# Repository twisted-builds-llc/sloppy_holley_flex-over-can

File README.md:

# Sloppy Holley Flex-over-CAN

CAN bus input/output module for Holley Terminator X (also HP/Dominator class ECUs).

- **To Holley:** GM/Continental flex-fuel sensor (ethanol % + fuel temp) and four 0-5 V analog inputs, sent as CAN device 1985.
- **From Holley:** four low-side (ground-switching) outputs, each on/off or PWM, following Holley I/O output rows.
- ESP32-C3-WROOM-02, WiFi AP web panel for status/config/test, USB-C for flashing.
- Built for JLCPCB assembly.

> Status: early development. See [docs/PROGRESS.md](docs/PROGRESS.md).
> Never use for engine control until the bench and engine-off validations in PROGRESS.md are complete.

## Connector (J1, HCCPHPE24BKA90F, 24 pin)

Cavity names are the J1 footprint pad names (rows A, B, C). Use them when building the harness.

| Cavity | Function | Cavity | Function | Cavity | Function |
|-------:|----------|-------:|----------|-------:|----------|
| A1 | +12 V in | B1 | Power GND | C1 | Output 3 (low side) |
| A2 | CAN H | B2 | +5 V sensor | C2 | +5 V sensor |
| A3 | CAN L | B3 | Analog 1 signal | C3 | Analog 3 signal |
| A4 | Flex sensor +12 V out | B4 | Sensor GND | C4 | Sensor GND |
| A5 | Flex sensor signal | B5 | +5 V sensor | C5 | +5 V sensor |
| A6 | Flex sensor GND | B6 | Analog 2 signal | C6 | Analog 4 signal |
| A7 | Power GND | B7 | Sensor GND | C7 | Sensor GND |
| A8 | Output 1 (low side) | B8 | Output 2 (low side) | C8 | Output 4 (low side) |

Output load current returns through A7 and B1. Sensor grounds (A6, B4, B7, C4, C7) are a separate quiet ground joined to power GND at one point on the board.

## Web panel

The module runs its own WiFi access point, `FLEXCAN-XXXX`. Each board makes a random password on first boot. Type `WIFI` on the USB serial console (115200) to see it. Then open http://192.168.4.1. The panel shows status and has controls for AUTO / ALL OFF, a 30 s output test, the Holley row for each output, and the WiFi password.

## Repository layout

| Path | Contents |
|------|----------|
| `docs/PROGRESS.md` | Phase checklist, work log, open questions |
| `docs/CAN_PROTOCOL.md` | Holley CAN IDs and encodings, marked verified or hypothesis |
| `docs/HARDWARE.md` | Block diagram, GPIO map, part choices |
| `firmware/` | PlatformIO project (VS Code) |
| `Sloppy_Holley_Flex-over-can/` | KiCad project and project-local libraries |
| `Holley_Canbus_info/` | Reference only: Holley CAN doc, DBC, and the two bench prototypes (`CANFLEXPDU_WiFi_Ver12`, `CAN_Flex_Slim_Ver5`) |

## Firmware build

Install the PlatformIO extension in VS Code, then open the `firmware/` folder. From a terminal:

```sh
cd firmware
pio run                 # build
pio run -t upload       # flash over USB-C
pio device monitor      # serial at 115200
pio test -e native      # host unit tests
```

The ESP32 platform is pinned to an exact release in `platformio.ini`. All code beyond the Arduino-ESP32 core lives in this repo, so a third-party library update cannot change the build.

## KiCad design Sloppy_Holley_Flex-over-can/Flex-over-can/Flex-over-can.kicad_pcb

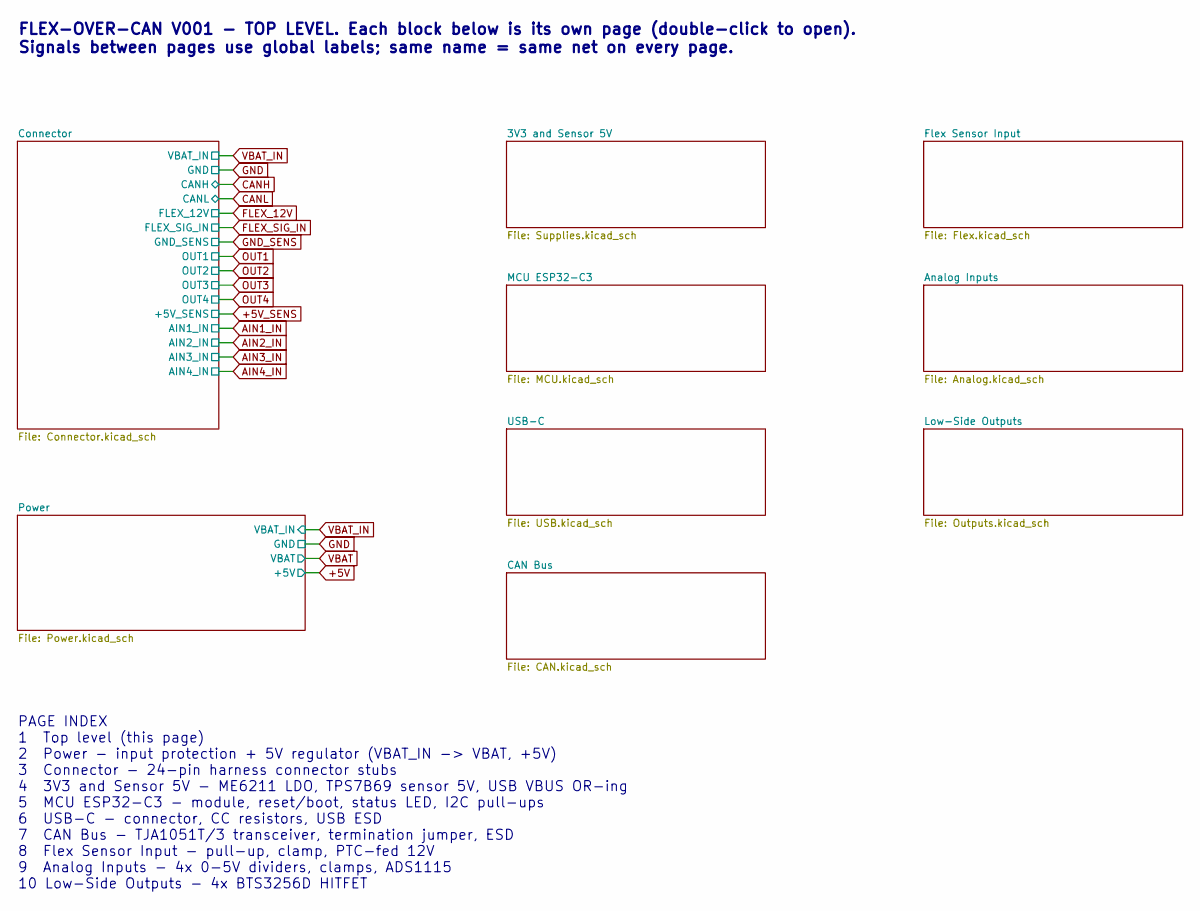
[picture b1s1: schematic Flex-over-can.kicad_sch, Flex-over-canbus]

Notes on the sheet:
PAGE INDEX 1 Top level (this page) 2 Power - input protection + 5V regulator (VBAT_IN -> VBAT, +5V) 3 Connector - 24-pin harness connector stubs 4 3V3 and Sensor 5V - ME6211 LDO, TPS7B69 sensor 5V, USB VBUS OR-ing 5 MCU ESP32-C3 - module, reset/boot, status LED, I2C pull-ups 6 USB-C - connector, CC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
FLEX-OVER-CAN V001 - TOP LEVEL. Each block below is its own page (double-click to open). Signals between pages use global labels; same name = same net on every page.

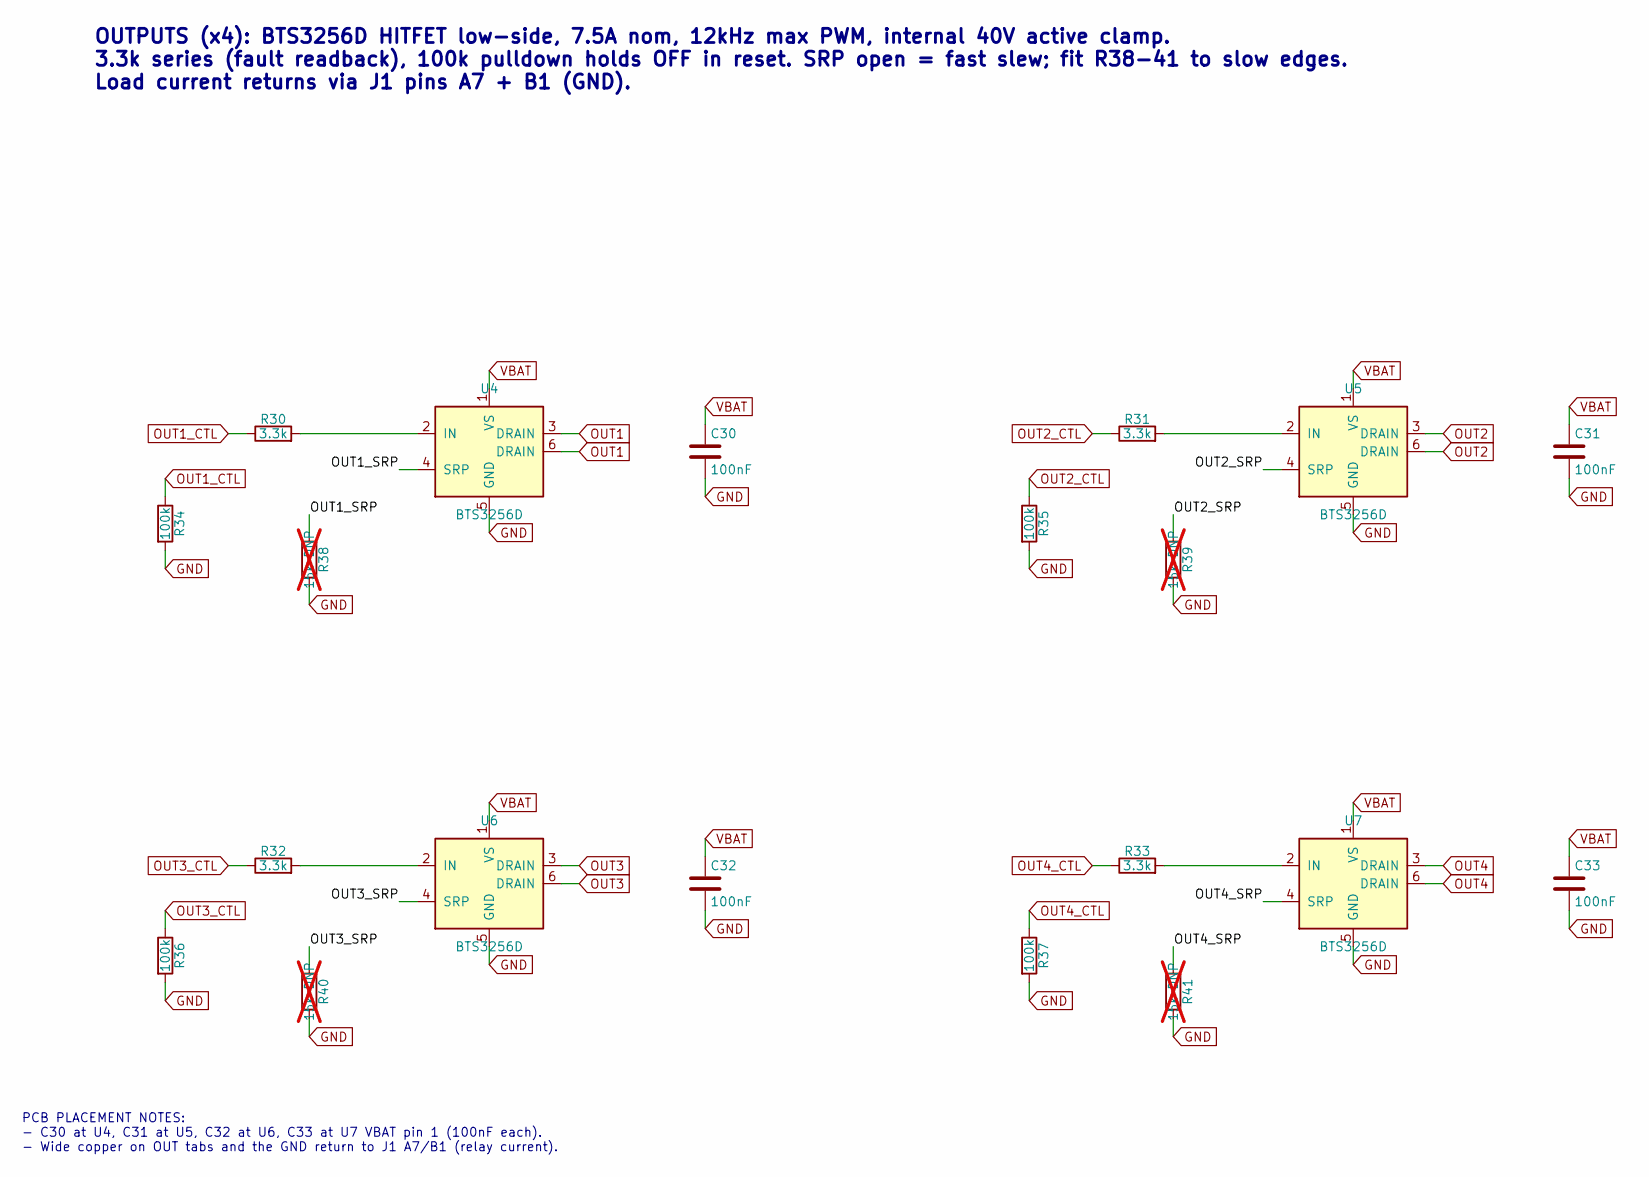
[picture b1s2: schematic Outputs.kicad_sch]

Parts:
C30, C31, C32, C33: 100nF; C_0603_1608Metric; LCSC C14663
R30, R31, R32, R33: 3.3k; R_0603_1608Metric; LCSC C22978
R34, R35, R36, R37: 100k; R_0603_1608Metric; LCSC C25803
R38, R39, R40, R41: 15k DNP; R_0603_1608Metric; LCSC C22809; not fitted
U4, U5, U6, U7: BTS3256D; TO-252-5_TabPin6; LCSC C3232337

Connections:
/Low-Side Outputs/OUT1_SRP: R38.1, U4.4 (SRP)
/Low-Side Outputs/OUT2_SRP: R39.1, U5.4 (SRP)
/Low-Side Outputs/OUT3_SRP: R40.1, U6.4 (SRP)
/Low-Side Outputs/OUT4_SRP: R41.1, U7.4 (SRP)
GND: C30.2, C31.2, C32.2, C33.2, R34.2, R35.2, R36.2, R37.2, R38.2, R39.2, R40.2, R41.2, U4.5 (GND), U5.5 (GND), U6.5 (GND), U7.5 (GND); also elsewhere on the board
unnamed: R30.2, U4.2 (IN)
unnamed: R31.2, U5.2 (IN)
unnamed: R32.2, U6.2 (IN)
unnamed: R33.2, U7.2 (IN)
OUT1: U4.3 (DRAIN), U4.6 (DRAIN); also elsewhere on the board
OUT1_CTL: R30.1, R34.1; also elsewhere on the board
OUT2: U5.3 (DRAIN), U5.6 (DRAIN); also elsewhere on the board
OUT2_CTL: R31.1, R35.1; also elsewhere on the board
OUT3: U6.3 (DRAIN), U6.6 (DRAIN); also elsewhere on the board
OUT3_CTL: R32.1, R36.1; also elsewhere on the board
OUT4: U7.3 (DRAIN), U7.6 (DRAIN); also elsewhere on the board
OUT4_CTL: R33.1, R37.1; also elsewhere on the board
VBAT: C30.1, C31.1, C32.1, C33.1, U4.1 (VS), U5.1 (VS), U6.1 (VS), U7.1 (VS); also elsewhere on the board

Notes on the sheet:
PCB PLACEMENT NOTES: - C30 at U4, C31 at U5, C32 at U6, C33 at U7 VBAT pin 1 (100nF each). - Wide copper on OUT tabs and the GND return to J1 A7/B1 (relay current).
OUTPUTS (x4): BTS3256D HITFET low-side, 7.5A nom, 12kHz max PWM, internal 40V active clamp. 3.3k series (fault readback), 100k pulldown holds OFF in reset. SRP open = fast slew; fit R38-41 to slow edges. Load current returns via J1 pins A7 + B1 (GND).

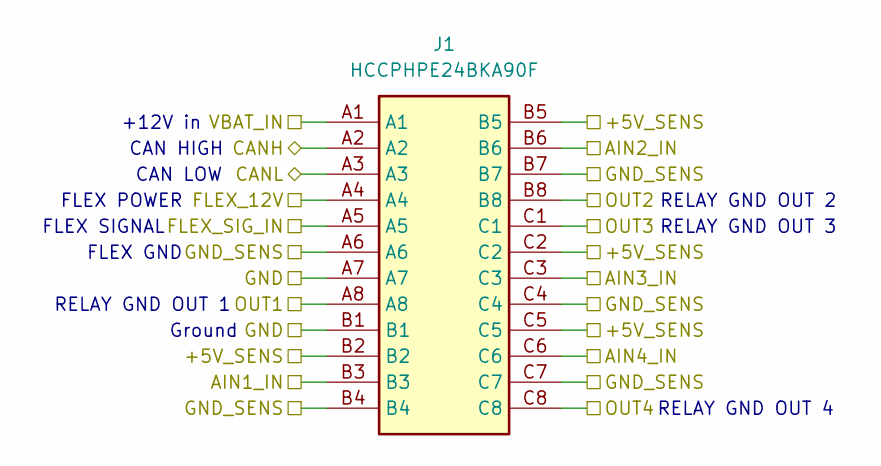
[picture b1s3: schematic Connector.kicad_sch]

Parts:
J1: HCCPHPE24BKA90F; 24pinConnectorFootprint; Manufacturer_Part_Number HCCPHPE24BKA90F; Mouser Part Number 649-HCCPHPE24BKA90F

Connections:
+5V_SENS: J1.B2, J1.B5, J1.C2, J1.C5; also elsewhere on the board
AIN1_IN: J1.B3; also elsewhere on the board
AIN2_IN: J1.B6; also elsewhere on the board
AIN3_IN: J1.C3; also elsewhere on the board
AIN4_IN: J1.C6; also elsewhere on the board
CANH: J1.A2; also elsewhere on the board
CANL: J1.A3; also elsewhere on the board
FLEX_12V: J1.A4; also elsewhere on the board
FLEX_SIG_IN: J1.A5; also elsewhere on the board
GND: J1.A7, J1.B1; also elsewhere on the board
GND_SENS: J1.A6, J1.B4, J1.B7, J1.C4, J1.C7; also elsewhere on the board
OUT1: J1.A8; also elsewhere on the board
OUT2: J1.B8; also elsewhere on the board
OUT3: J1.C1; also elsewhere on the board
OUT4: J1.C8; also elsewhere on the board
VBAT_IN: J1.A1; also elsewhere on the board

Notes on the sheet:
FLEX SIGNAL
RELAY GND OUT 2
+12V in
FLEX GND
RELAY GND OUT 3
Ground
CAN HIGH
RELAY GND OUT 1
FLEX POWER
CAN LOW
RELAY GND OUT 4

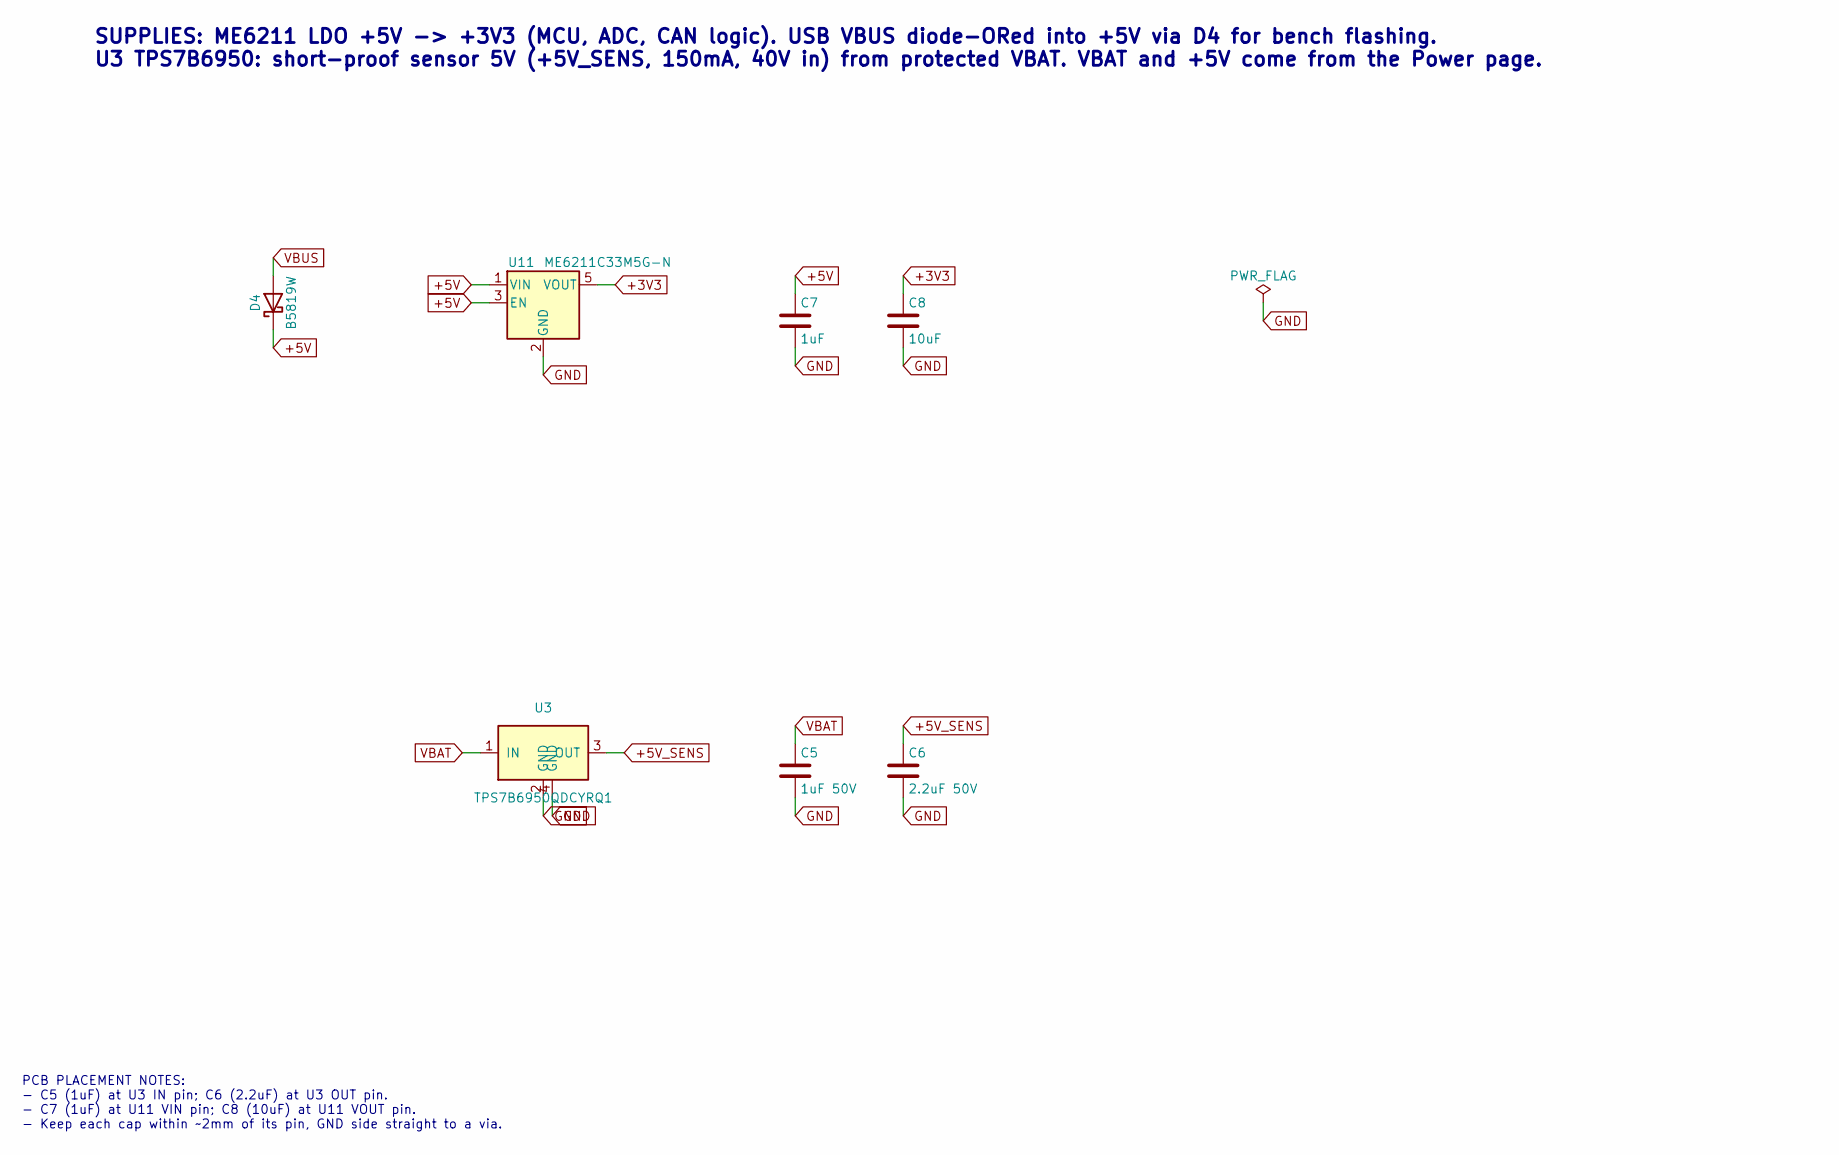
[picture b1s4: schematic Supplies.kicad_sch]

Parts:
C5: 1uF 50V; C_0805_2012Metric; LCSC C28323
C6: 2.2uF 50V; C_0805_2012Metric; LCSC C377773
C7: 1uF; C_0603_1608Metric; LCSC C15849
C8: 10uF; C_0603_1608Metric; LCSC C19702
D4: B5819W; D_SOD-123; LCSC C2943878
U3: TPS7B6950QDCYRQ1; SOT-223; LCSC C108469
U11: ME6211C33M5G-N; SOT-23-5; LCSC C82942

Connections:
+3V3: C8.1, U11.5 (VOUT); also elsewhere on the board
+5V: C7.1, D4.1 (K), U11.1 (VIN), U11.3 (EN); also elsewhere on the board
+5V_SENS: C6.1, U3.3 (OUT); also elsewhere on the board
GND: C5.2, C6.2, C7.2, C8.2, U3.2 (GND), U3.4 (GND), U11.2 (GND); also elsewhere on the board
VBAT: C5.1, U3.1 (IN); also elsewhere on the board
VBUS: D4.2 (A); also elsewhere on the board

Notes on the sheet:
PCB PLACEMENT NOTES: - C5 (1uF) at U3 IN pin; C6 (2.2uF) at U3 OUT pin. - C7 (1uF) at U11 VIN pin; C8 (10uF) at U11 VOUT pin. - Keep each cap within ~2mm of its pin, GND side straight to a via.
SUPPLIES: ME6211 LDO +5V -> +3V3 (MCU, ADC, CAN logic). USB VBUS diode-ORed into +5V via D4 for bench flashing. U3 TPS7B6950: short-proof sensor 5V (+5V_SENS, 150mA, 40V in) from protected VBAT. VBAT and +5V come from the Power page.

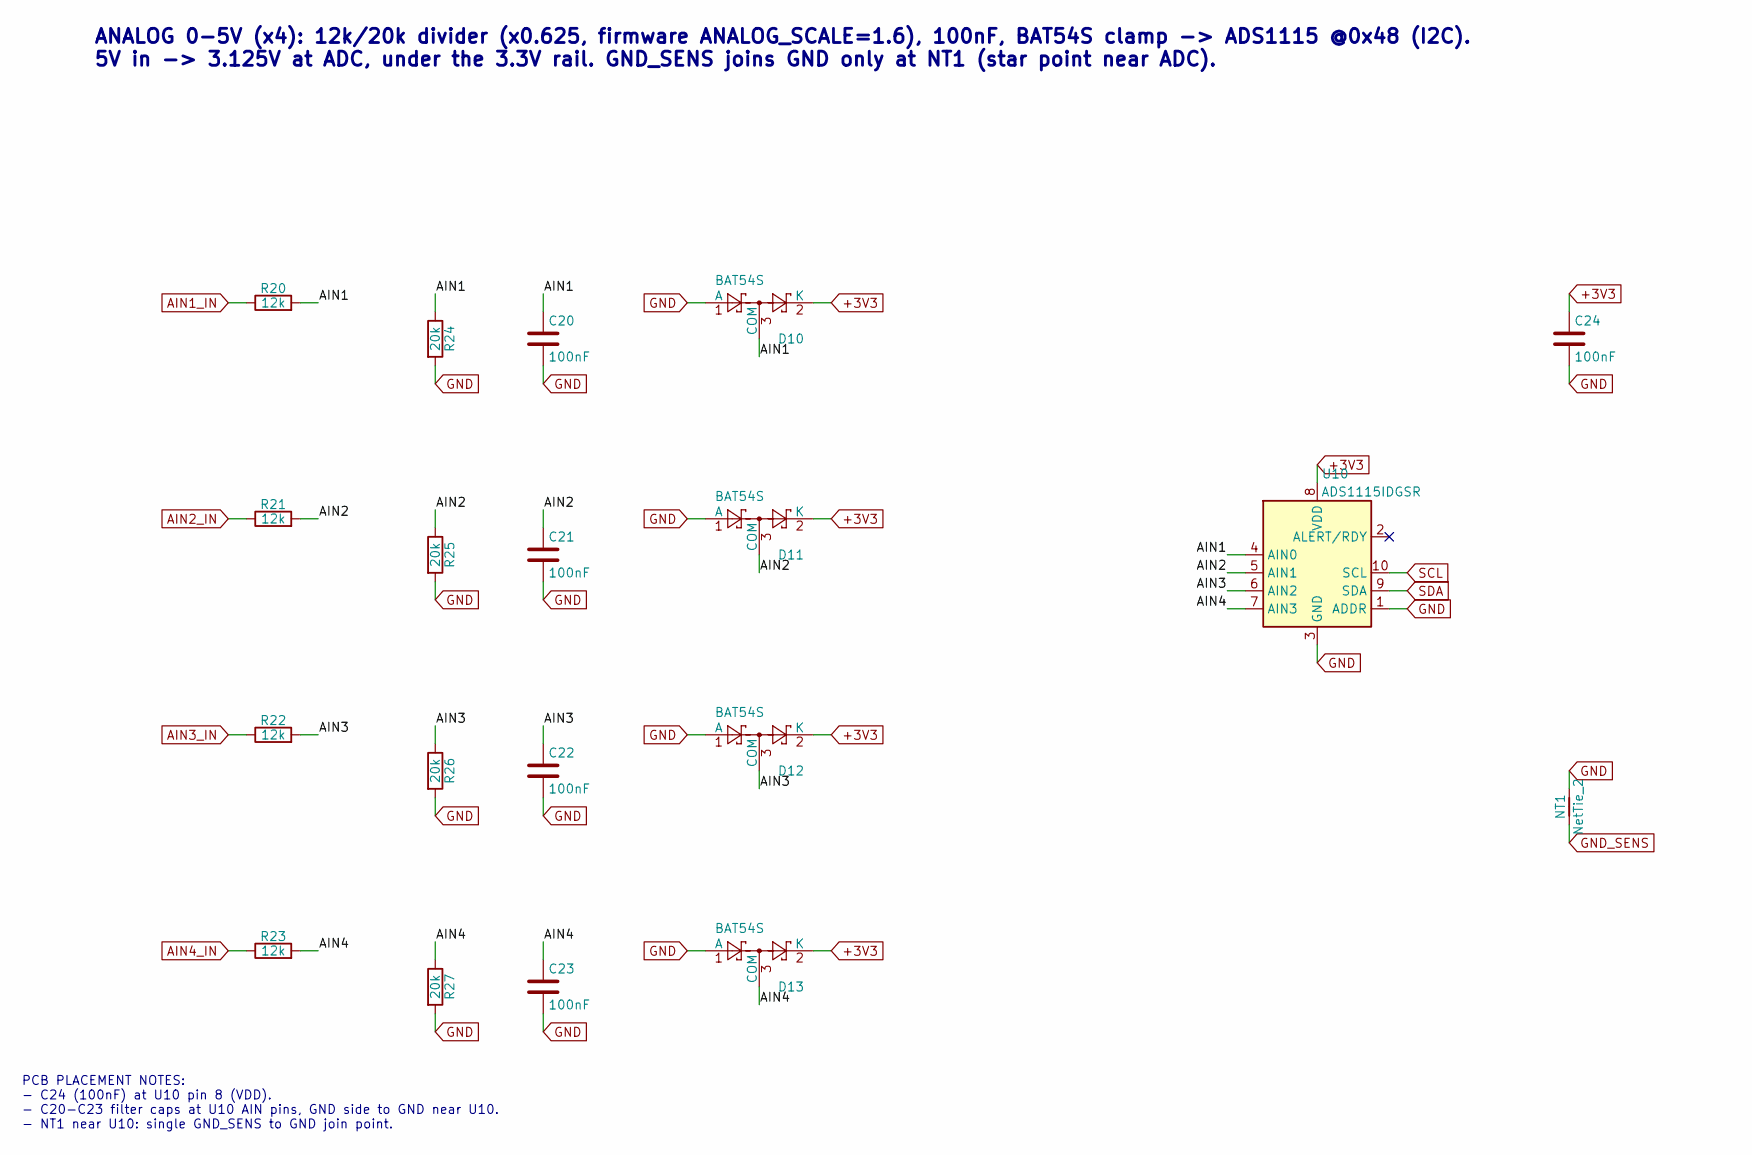
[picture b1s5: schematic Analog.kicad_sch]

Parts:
C20, C21, C22, C23, C24: 100nF; C_0603_1608Metric; LCSC C14663
D10, D11, D12, D13: BAT54S; SOT-23; LCSC C7420333
NT1: NetTie_2; NetTie-2_SMD_Pad0.5mm
R20, R21, R22, R23: 12k; R_0603_1608Metric; LCSC C22790
R24, R25, R26, R27: 20k; R_0603_1608Metric; LCSC C4184
U10: ADS1115IDGSR; TSSOP-10_3x3mm_P0.5mm; LCSC C37593

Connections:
+3V3: C24.1, D10.2 (K), D11.2 (K), D12.2 (K), D13.2 (K), U10.8 (VDD); also elsewhere on the board
/Analog Inputs/AIN1: C20.1, D10.3 (COM), R20.2, R24.1, U10.4 (AIN0)
/Analog Inputs/AIN2: C21.1, D11.3 (COM), R21.2, R25.1, U10.5 (AIN1)
/Analog Inputs/AIN3: C22.1, D12.3 (COM), R22.2, R26.1, U10.6 (AIN2)
/Analog Inputs/AIN4: C23.1, D13.3 (COM), R23.2, R27.1, U10.7 (AIN3)
AIN1_IN: R20.1; also elsewhere on the board
AIN2_IN: R21.1; also elsewhere on the board
AIN3_IN: R22.1; also elsewhere on the board
AIN4_IN: R23.1; also elsewhere on the board
GND: C20.2, C21.2, C22.2, C23.2, C24.2, D10.1 (A), D11.1 (A), D12.1 (A), D13.1 (A), NT1.2, R24.2, R25.2, R26.2, R27.2, U10.1 (ADDR), U10.3 (GND); also elsewhere on the board
GND_SENS: NT1.1; also elsewhere on the board
SCL: U10.10 (SCL); also elsewhere on the board
SDA: U10.9 (SDA); also elsewhere on the board

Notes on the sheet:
ANALOG 0-5V (x4): 12k/20k divider (x0.625, firmware ANALOG_SCALE=1.6), 100nF, BAT54S clamp -> ADS1115 @0x48 (I2C). 5V in -> 3.125V at ADC, under the 3.3V rail. GND_SENS joins GND only at NT1 (star point near ADC).
PCB PLACEMENT NOTES: - C24 (100nF) at U10 pin 8 (VDD). - C20-C23 filter caps at U10 AIN pins, GND side to GND near U10. - NT1 near U10: single GND_SENS to GND join point.

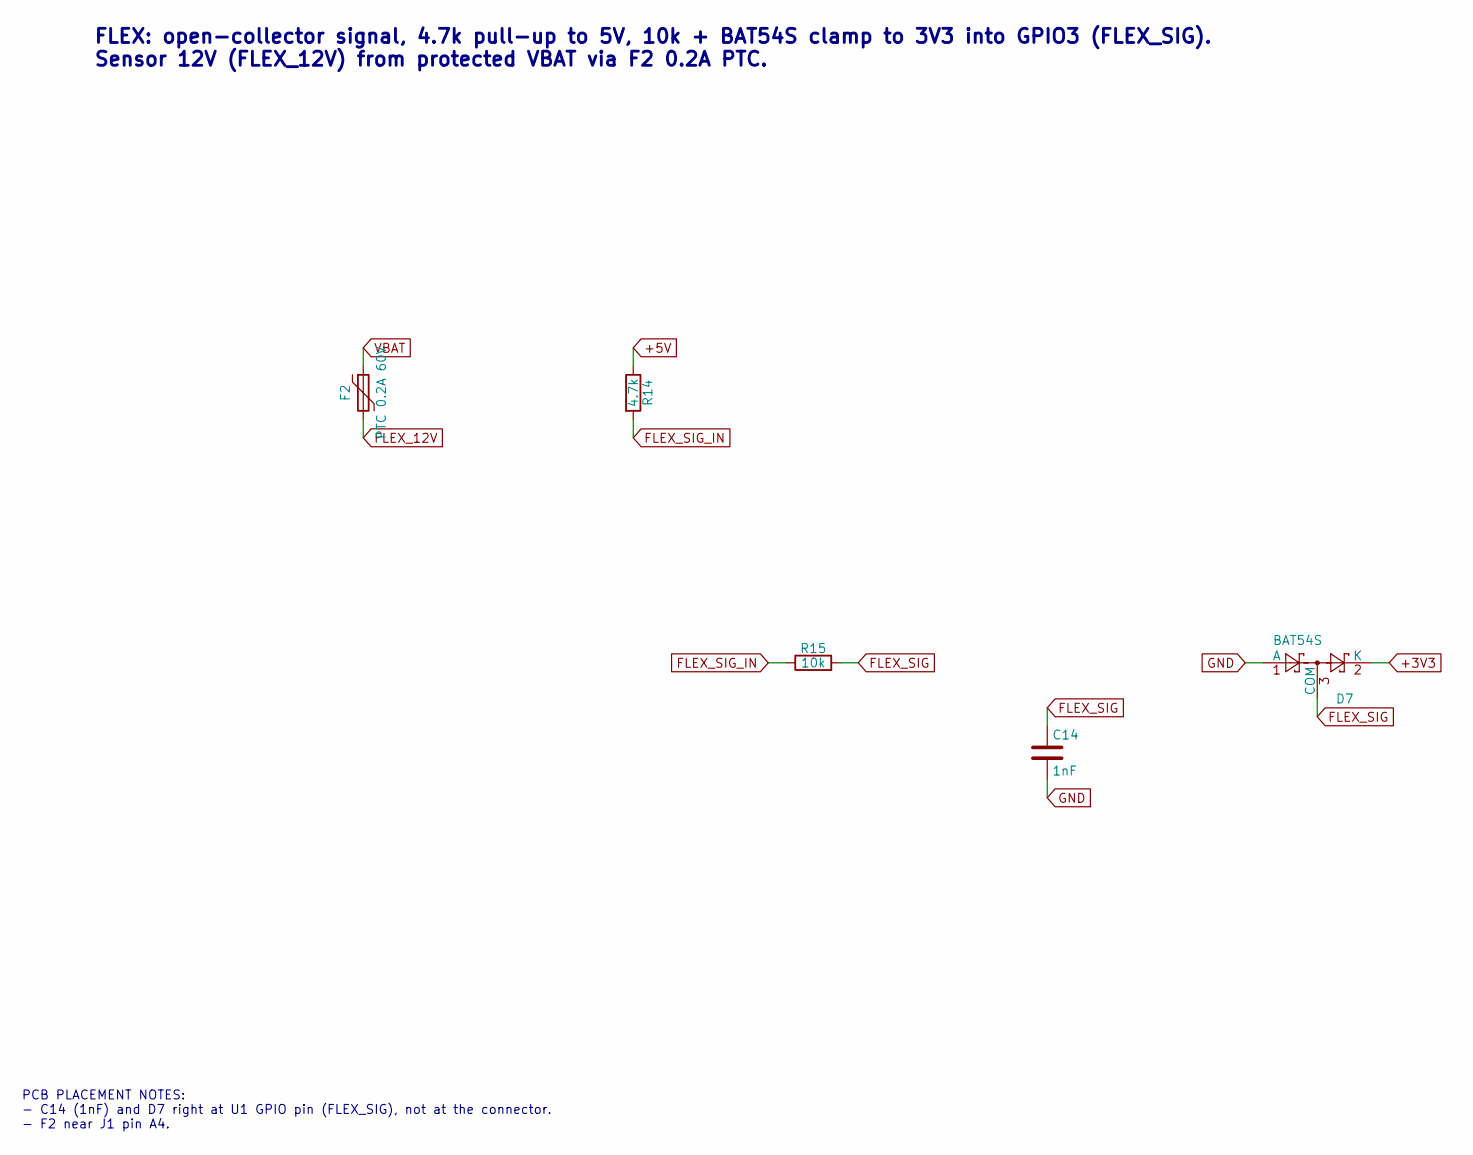
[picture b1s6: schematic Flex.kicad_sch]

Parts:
C14: 1nF; C_0603_1608Metric; LCSC C1588
D7: BAT54S; SOT-23; LCSC C7420333
F2: PTC 0.2A 60V; Fuse_1812_4532Metric; MPN SMD1812B020TF-J; LCSC C269125
R14: 4.7k; R_0603_1608Metric; LCSC C23162
R15: 10k; R_0603_1608Metric; LCSC C25804

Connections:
+3V3: D7.2 (K); also elsewhere on the board
+5V: R14.1; also elsewhere on the board
FLEX_12V: F2.2; also elsewhere on the board
FLEX_SIG: C14.1, D7.3 (COM), R15.2; also elsewhere on the board
FLEX_SIG_IN: R14.2, R15.1; also elsewhere on the board
GND: C14.2, D7.1 (A); also elsewhere on the board
VBAT: F2.1; also elsewhere on the board

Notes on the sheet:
FLEX: open-collector signal, 4.7k pull-up to 5V, 10k + BAT54S clamp to 3V3 into GPIO3 (FLEX_SIG). Sensor 12V (FLEX_12V) from protected VBAT via F2 0.2A PTC.
PCB PLACEMENT NOTES: - C14 (1nF) and D7 right at U1 GPIO pin (FLEX_SIG), not at the connector. - F2 near J1 pin A4.

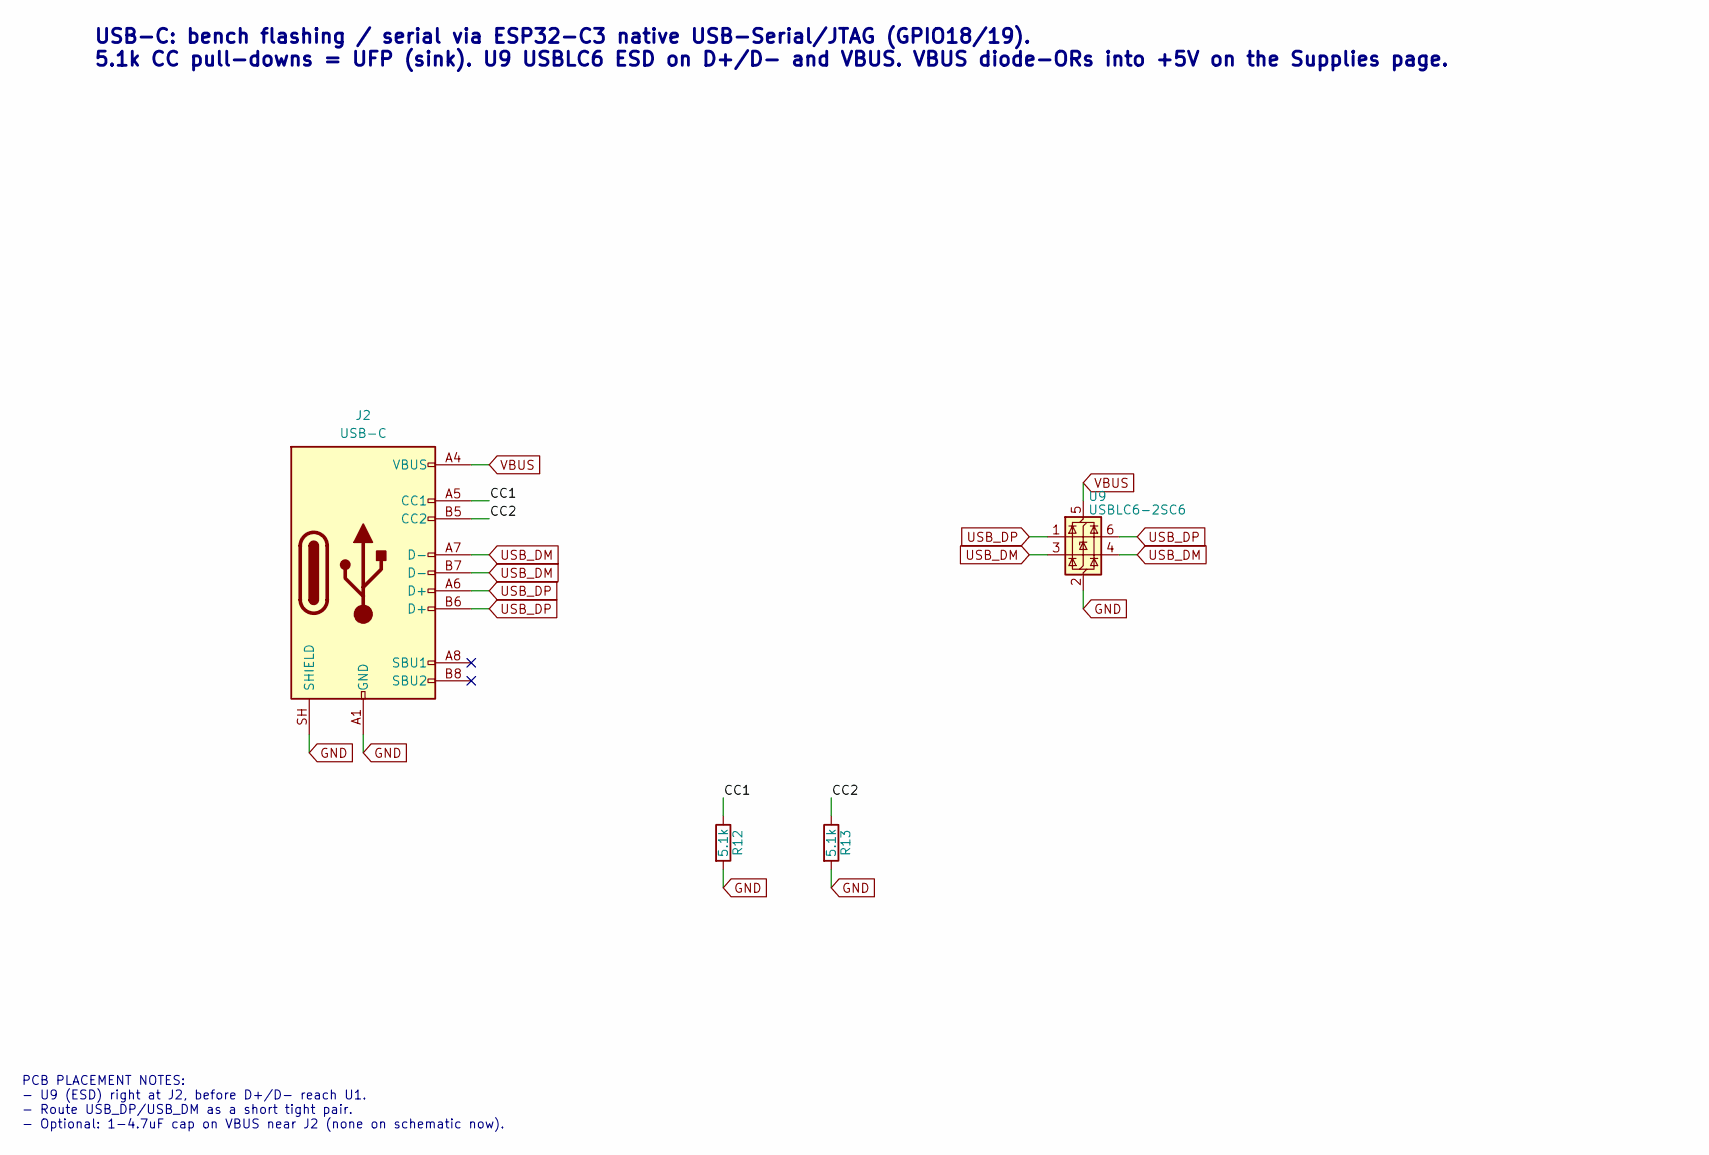
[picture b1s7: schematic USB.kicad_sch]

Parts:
J2: USB-C; USB_C_Receptacle_HRO_TYPE-C-31-M-12; LCSC C165948
R12, R13: 5.1k; R_0603_1608Metric; LCSC C23186
U9: USBLC6-2SC6; SOT-23-6; LCSC C7519

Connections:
/USB-C/CC1: J2.A5 (CC1), R12.1
/USB-C/CC2: J2.B5 (CC2), R13.1
GND: J2.A1 (GND), J2.A12 (GND), J2.B1 (GND), J2.B12 (GND), J2.SH (SHIELD), R12.2, R13.2, U9.2 (GND); also elsewhere on the board
USB_DM: J2.A7 (D-), J2.B7 (D-), U9.3 (I/O2), U9.4 (I/O2); also elsewhere on the board
USB_DP: J2.A6 (D+), J2.B6 (D+), U9.1 (I/O1), U9.6 (I/O1); also elsewhere on the board
VBUS: J2.A4 (VBUS), J2.A9 (VBUS), J2.B4 (VBUS), J2.B9 (VBUS), U9.5 (VBUS); also elsewhere on the board

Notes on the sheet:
PCB PLACEMENT NOTES: - U9 (ESD) right at J2, before D+/D- reach U1. - Route USB_DP/USB_DM as a short tight pair. - Optional: 1-4.7uF cap on VBUS near J2 (none on schematic now).
USB-C: bench flashing / serial via ESP32-C3 native USB-Serial/JTAG (GPIO18/19). 5.1k CC pull-downs = UFP (sink). U9 USBLC6 ESD on D+/D- and VBUS. VBUS diode-ORs into +5V on the Supplies page.

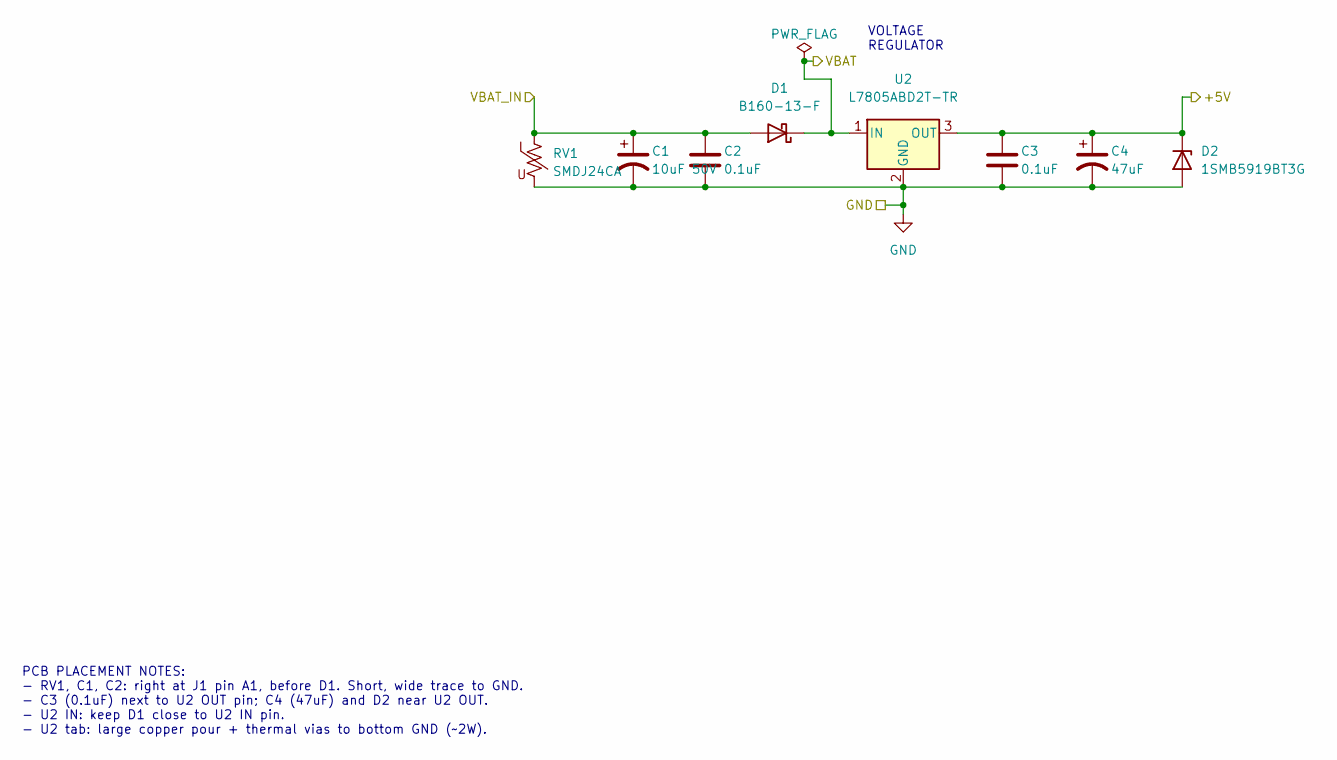
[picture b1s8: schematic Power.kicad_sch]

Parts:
C1: 10uF 50V; C_1206_3216Metric; LCSC C13585
C2, C3: 0.1uF; C_0805_2012Metric; LCSC C49678
C4: 47uF; CP_EIA-3528-21_Kemet-B; LCSC C136751
D1: B160-13-F; D_SMA; LCSC C24784
D2: 1SMB5919BT3G; D_SMB; LCSC C70260
RV1: SMDJ24CA; D_SMC; LCSC C215903
U2: L7805ABD2T-TR; TO-263-2; LCSC C86206

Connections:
+5V: C3.1, C4.1, D2.1 (K), U2.3 (OUT); also elsewhere on the board
GND: C1.2, C2.2, C3.2, C4.2, D2.2 (A), RV1.2, U2.2 (GND); also elsewhere on the board
VBAT: D1.1 (K), U2.1 (IN); also elsewhere on the board
VBAT_IN: C1.1, C2.1, D1.2 (A), RV1.1; also elsewhere on the board

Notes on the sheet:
PCB PLACEMENT NOTES: - RV1, C1, C2: right at J1 pin A1, before D1. Short, wide trace to GND. - C3 (0.1uF) next to U2 OUT pin; C4 (47uF) and D2 near U2 OUT. - U2 IN: keep D1 close to U2 IN pin. - U2 tab: large copper pour + thermal vias to bottom GND (~2W).
VOLTAGE REGULATOR

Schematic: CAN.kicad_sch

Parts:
C12, C13: 100nF; C_0603_1608Metric; LCSC C14663
D6: NUP2105L; SOT-23; LCSC C284104
JP1: CAN_TERM; SolderJumper-2_P1.3mm_Open_RoundedPad1.0x1.5mm
R10: 10k; R_0603_1608Metric; LCSC C25804
R11: 120; R_0603_1608Metric; LCSC C22787
U8: TJA1051T/3; SOIC-8_3.9x4.9mm_P1.27mm; LCSC C38695

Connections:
+3V3: C13.1, R10.1, U8.5 (VIO); also elsewhere on the board
+5V: C12.1, U8.3 (VCC); also elsewhere on the board
/CAN Bus/CAN_TERM: JP1.1 (A), R11.2
CANH: D6.1 (K), R11.1, U8.7 (CANH); also elsewhere on the board
CANL: D6.2 (K), JP1.2 (B), U8.6 (CANL); also elsewhere on the board
CAN_RX: U8.4 (RXD); also elsewhere on the board
CAN_S: R10.2, U8.8 (S); also elsewhere on the board
CAN_TX: U8.1 (TXD); also elsewhere on the board
GND: C12.2, C13.2, D6.3 (A), U8.2 (GND); also elsewhere on the board

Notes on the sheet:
PCB PLACEMENT NOTES: - C12 (100nF) at U8 pin 3 (VCC 5V); C13 (100nF) at U8 pin 5 (VIO 3V3). - D6, R11, JP1 close to J1 CANH/CANL pins. - Route CANH/CANL as a tight pair.
CAN: TJA1051T/3 (VCC +5V, VIO +3V3). S pulled high = silent until firmware drives GPIO21 low. JP1 bridges 120R termination (default open). D6 NUP2105L ESD on CANH/CANL.

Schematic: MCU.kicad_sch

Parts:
C9: 10uF; C_0603_1608Metric; LCSC C19702
C10: 100nF; C_0603_1608Metric; LCSC C14663
C11: 1uF; C_0603_1608Metric; LCSC C15849
D5: STATUS; LED_0603_1608Metric; LCSC C2286
R4, R5, R6: 10k; R_0603_1608Metric; LCSC C25804
R7: 1k; R_0603_1608Metric; LCSC C21190
R8, R9: 4.7k; R_0603_1608Metric; LCSC C23162
SW1: BOOT; SW_Push_1P1T_XKB_TS-1187A; LCSC C318884
U1: ESP32-C3-WROOM-02-N4; ESP32-C3-WROOM-02; LCSC C2934560

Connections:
+3V3: C9.1, C10.1, R4.1, R5.1, R6.1, R7.1, R8.1, R9.1, U1.1 (3V3); also elsewhere on the board
/MCU ESP32-C3/BOOT: R5.2, SW1.1, U1.8 (IO9)
/MCU ESP32-C3/EN: C11.1, R4.2, U1.2 (EN)
/MCU ESP32-C3/LED_A: D5.2 (A), R7.2
/MCU ESP32-C3/STATUS_LED: D5.1 (K), R6.2, U1.16 (IO2)
CAN_RX: U1.4 (IO5); also elsewhere on the board
CAN_S: U1.12 (IO21/TXD); also elsewhere on the board
CAN_TX: U1.3 (IO4); also elsewhere on the board
FLEX_SIG: U1.15 (IO3); also elsewhere on the board
GND: C9.2, C10.2, C11.2, SW1.2, U1.9 (GND), U1.19 (GND); also elsewhere on the board
OUT1_CTL: U1.18 (IO0); also elsewhere on the board
OUT2_CTL: U1.17 (IO1); also elsewhere on the board
OUT3_CTL: U1.6 (IO7); also elsewhere on the board
OUT4_CTL: U1.10 (IO10); also elsewhere on the board
SCL: R9.2, U1.5 (IO6); also elsewhere on the board
SDA: R8.2, U1.7 (IO8); also elsewhere on the board
USB_DM: U1.13 (IO18); also elsewhere on the board
USB_DP: U1.14 (IO19); also elsewhere on the board

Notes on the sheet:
PCB PLACEMENT NOTES: - C10 (100nF) at U1 pin 3 (3V3), smallest loop to GND pad. - C9 (10uF) next to C10, same 3V3 pin. - C11 (1uF) at U1 pin 8 (EN). - Keep-out: no copper or parts under/near U1 antenna end.
MCU: ESP32-C3-MINI-1-N4. EN RC (R4/C11) for clean reset. GPIO9 = BOOT (SW1 to GND, R5 pull-up). Strap pins GPIO2 (status LED, R6 pull-up) and GPIO8 (SDA, R8 I2C pull-up) idle high at boot. GPIO20 spare. GPIO21 (U0TXD) drives CAN_S: idles high through boot = transceiver silent.

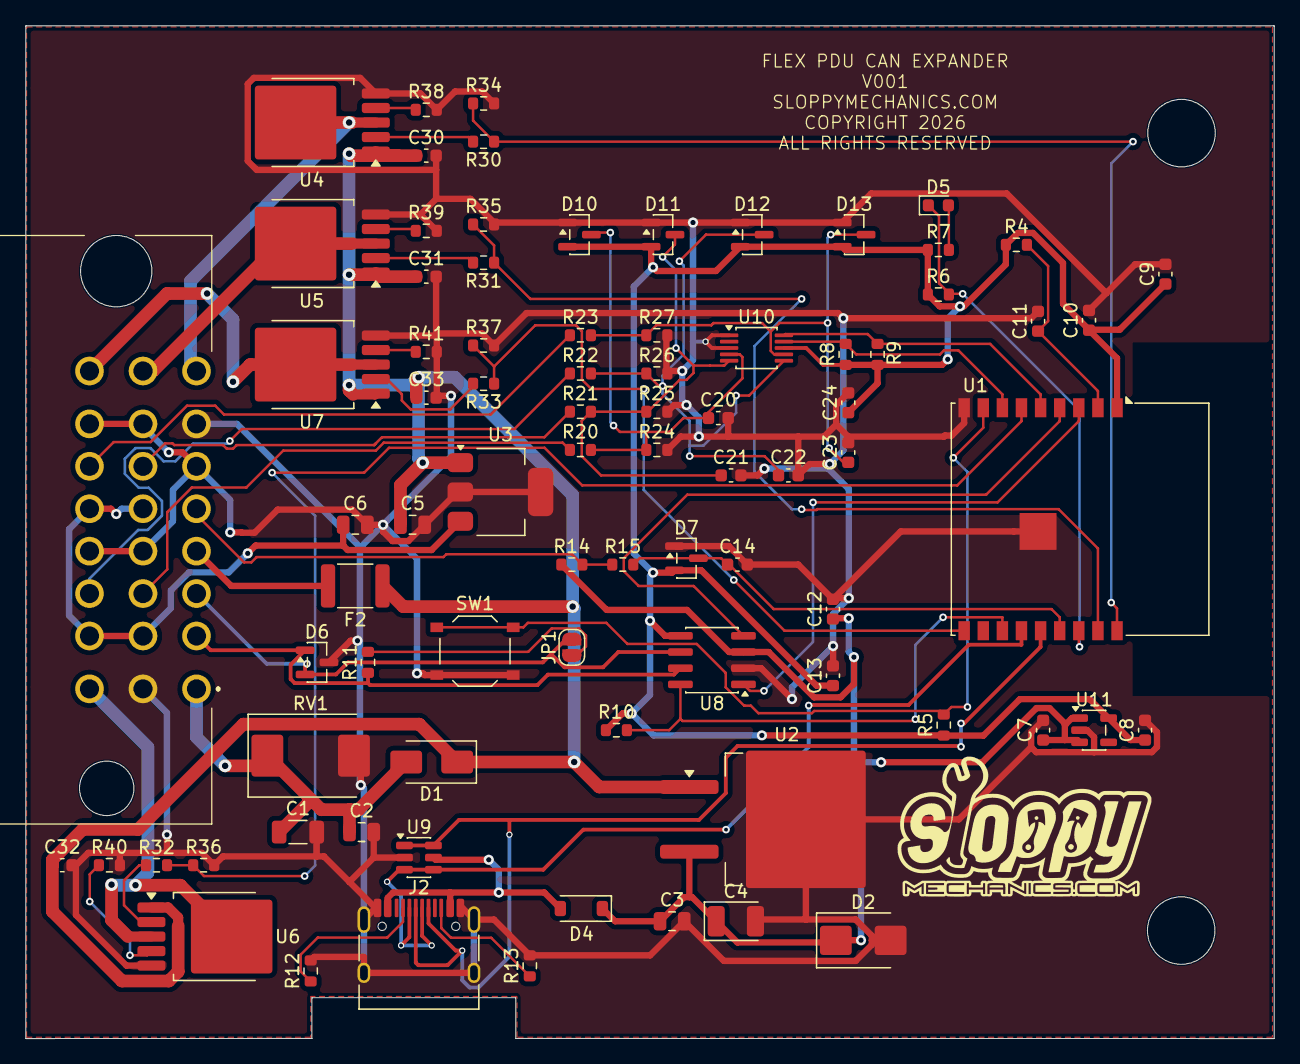
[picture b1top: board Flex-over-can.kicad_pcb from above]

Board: 2 copper layers, 98.0 x 79.5 mm, 85 parts (0 on the bottom side), 51 nets.

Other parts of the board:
HOLE1, HOLE2: MountingHole_5.3mm_M5

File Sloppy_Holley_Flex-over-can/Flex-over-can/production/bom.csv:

Designator,Footprint,Quantity,Value,LCSC Part #
C1,1206,1,10uF 50V,C13585
"C10, C12, C13, C20, C21, C22, C23, C24, C30, C31, C32, C33",0603,12,100nF,C14663
"C11, C7",0603,2,1uF,C15849
C14,0603,1,1nF,C1588
"C2, C3",0805,2,0.1uF,C49678
C4,CP_EIA-3528-21_Kemet-B,1,47uF,C136751
C5,0805,1,1uF 50V,C28323
C6,0805,1,2.2uF 50V,C377773
"C8, C9",0603,2,10uF,C19702
D1,D_SMA,1,B160-13-F,C24784
"D10, D11, D12, D13, D7",SOT-23,5,BAT54S,C7420333
D2,D_SMB,1,1SMB5919BT3G,C70260
D4,D_SOD-123,1,B5819W,C2943878
D5,0603,1,STATUS,C2286
D6,SOT-23,1,NUP2105L,C284104
F2,1812,1,PTC 0.2A 60V,C269125
J2,USB_C_Receptacle_HRO_TYPE-C-31-M-12,1,USB-C,C165948
JP1,SolderJumper-2_P1.3mm_Open_RoundedPad1.0x1.5mm,1,CAN_TERM,
NT1,NetTie-2_SMD_Pad0.5mm,1,NetTie_2,
"R10, R15, R4, R5, R6",0603,5,10k,C25804
R11,0603,1,120,C22787
"R12, R13",0603,2,5.1k,C23186
"R14, R8, R9",0603,3,4.7k,C23162
"R20, R21, R22, R23",0603,4,12k,C22790
"R24, R25, R26, R27",0603,4,20k,C4184
"R30, R31, R32, R33",0603,4,3.3k,C22978
"R34, R35, R36, R37",0603,4,100k,C25803
R7,0603,1,1k,C21190
RV1,D_SMC,1,SMDJ24CA,C215903
SW1,SW_Push_1P1T_XKB_TS-1187A,1,BOOT,C318884
U1,ESP32-C3-WROOM-02,1,ESP32-C3-WROOM-02-N4,C2934560
U10,TSSOP-10_3x3mm_P0.5mm,1,ADS1115IDGSR,C37593
U11,SOT-23-5,1,ME6211C33M5G-N,C82942
U2,TO-263-2,1,L7805ABD2T-TR,C86206
U3,SOT-223,1,TPS7B6950QDCYRQ1,C108469
"U4, U5, U6, U7",TO-252-5_TabPin6,4,BTS3256D,C3232337
U8,SOIC-8_3.9x4.9mm_P1.27mm,1,TJA1051T/3,C38695
U9,SOT-23-6,1,USBLC6-2SC6,C7519

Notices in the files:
Sloppy_Holley_Flex-over-can/Flex-over-can/Flex-over-can.kicad_pcb:
COPYRIGHT 2026
ALL RIGHTS RESERVED
